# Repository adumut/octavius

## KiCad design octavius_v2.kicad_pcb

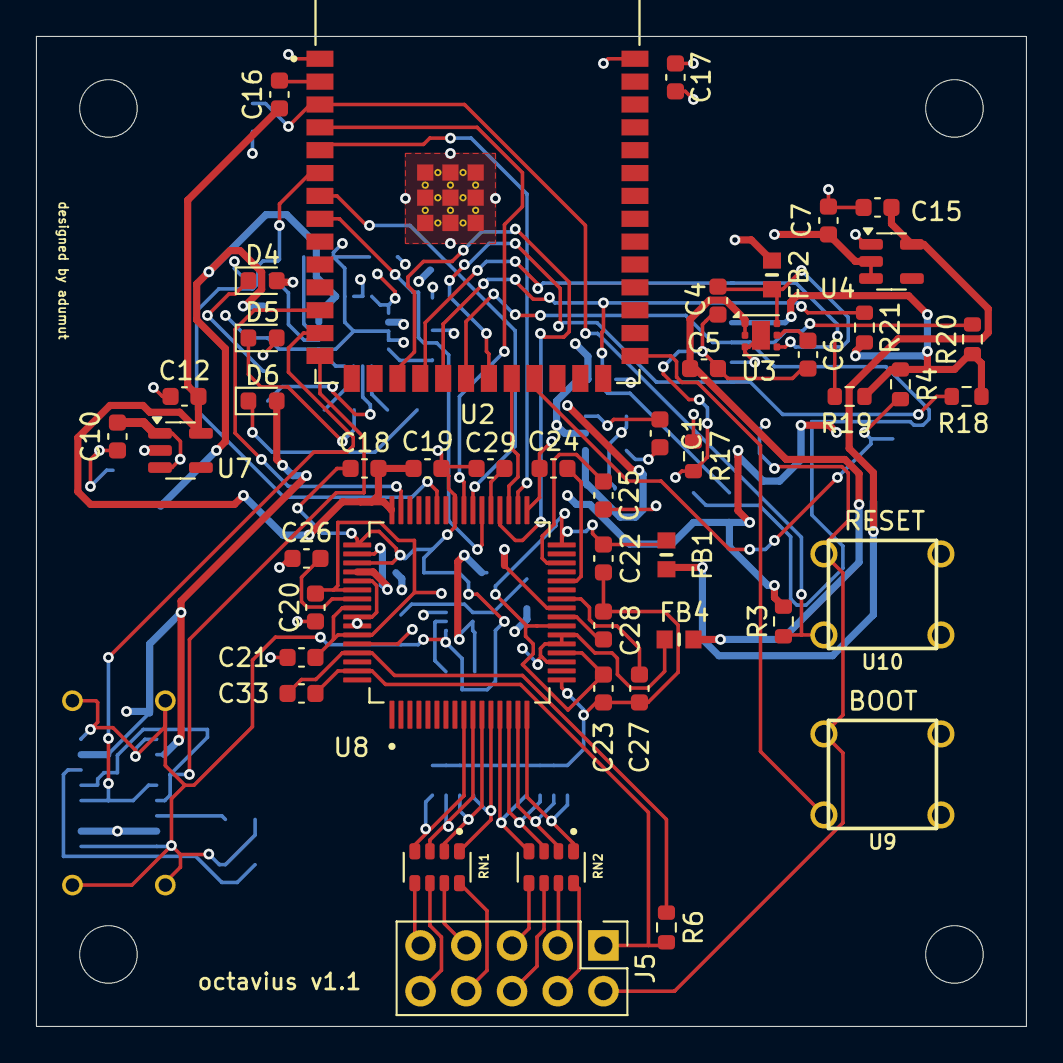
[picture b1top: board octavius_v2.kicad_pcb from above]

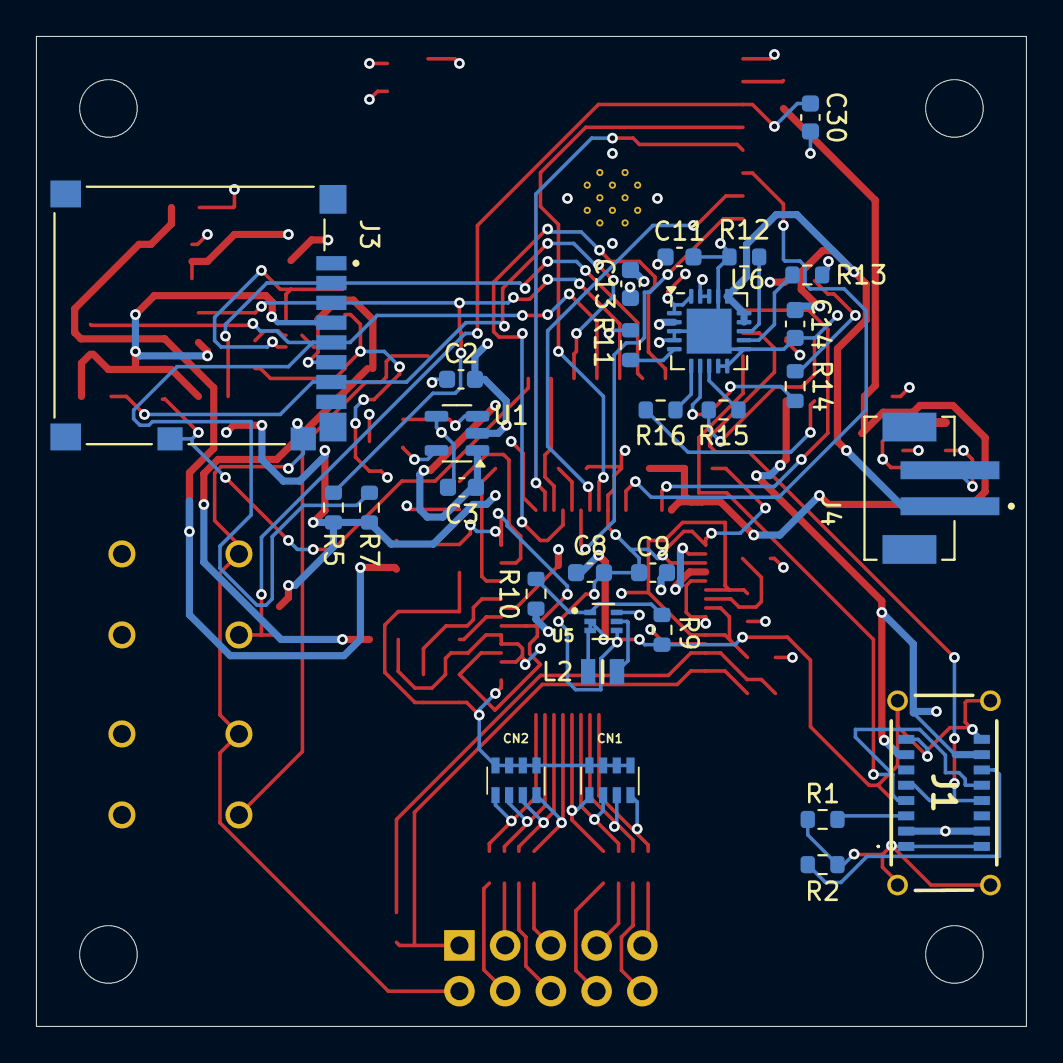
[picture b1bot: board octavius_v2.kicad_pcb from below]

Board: 4 copper layers, 55.0 x 55.0 mm, 76 parts (29 on the bottom side), 71 nets.

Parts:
C1, C2, C3, C6, C10, C12, C18, C21, C23, C25, C26, C27, C28, C30: 1uF; C_0603_1608Metric
C4, C5, C7, C15, C24: 2.2uF; C_0603_1608Metric
C8, C11, C16: 10uF; C_0603_1608Metric
C9: 22uF; C_0603_1608Metric
C13, C14: 4.7uF; C_0603_1608Metric
C17: 0.1uF; C_0603_1608Metric
C19, C20, C22: 100nF; C_0603_1608Metric
C29: 1nF; C_0603_1608Metric
C33: 1.5nF; C_0603_1608Metric
CN1, CN2: W3A45C103KAT2A (0.01uF); W3A45C103KAT2A
D4, D5, D6: LED; LED_0603_1608Metric
FB1, FB2, FB4: FerriteBead; BEADC1608X75N
J1: UJ20-C-V-SMT-TR-68; UJ20CVSMTTR68
J3: 5027740891; MOLEX_5027740891
J4: B2B-PH-SM4-TB; JST_B2B-PH-SM4-TB
J5: Conn_02x05_Odd_Even; PinHeader_2x05_P2.54mm_Vertical
L2: 2.2uH; DFE201210S1R0MP2
R1, R2: 5.1K; R_0603_1608Metric
R3, R4, R5, R7, R11, R18, R19, R20, R21: 10K; R_0603_1608Metric
R6: 1M; R_0603_1608Metric
R9: 100K; R_0603_1608Metric
R10: 732K; R_0603_1608Metric
R12, R13: 2K; R_0603_1608Metric
R14, R15, R16: 470; R_0603_1608Metric
R17: 0; R_0603_1608Metric
RN1, RN2: YC164-JR-072K2L (2.2K); YC164-JR-072K2L
U1: TPS60403DBV; SOT-23-5
U2: ESP32-S3-WROOM-1-N4R2
U3: ADP7118ACPZN; LFCSP-6-1EP_2x2mm_P0.65mm_EP1x1.6mm
U4: ADP7182AUJZ-2.5; TSOT-23-5
U5: TPS61023DRLT
U6: MCP73871; QFN-20-1EP_4x4mm_P0.5mm_EP2.5x2.5mm
U7: AP2112K-3.3; SOT-23-5
U8: ADS1299-4PAGR
U9, U10: JTP-1130

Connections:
1N: J5.3, RN2.7
1P: J5.4, RN2.8
2N: J5.5, RN2.5
2P: J5.6, RN2.6
3N: J5.7, RN1.7
3P: J5.8, RN1.8
4N: J5.9, RN1.5
4P: J5.10, RN1.6
-5V_RAW: C3.2, C7.2, U1.1 (OUT), U4.2 (VIN), U4.3 (EN)
/AFE/+2.5V_ANALOG: C5.1, FB4.2, U3.1 (VOUT), U3.2 (SENSE/ADJ)
/AFE/+3.3V: C12.2, C16.2, C18.2, C19.2, J3.4 (VDD), R3.2, R4.2, R5.1, R7.2, R18.2, R19.2, R20.1, R21.2, U7.5 (VOUT), U8.48 (DVDD), U8.50 (DVDD), U8.52 (CLKSEL)
/AFE/-2.5V_ANALOG: C15.2, FB1.1, U4.5 (VOUT), U8.25 (VREFN)
/AFE/AFE_CS: U2.7 (IO7), U8.39 (~CS)
/AFE/AFE_DRDY: U2.12 (IO8), U8.47 (~DRDY)
/AFE/AFE_MISO: U2.6 (IO6), U8.43 (DOUT)
/AFE/AFE_MOSI: U2.5 (IO5), U8.34 (DIN)
/AFE/AFE_RESET: U2.17 (IO9), U8.36 (~RESET)
/AFE/AFE_SCLK: U2.4 (IO4), U8.40 (SCLK)
/MCU_and_Connectors/USB_N: J1.A7 (DN1), J1.B7 (DN2), U2.13 (IO19)
/MCU_and_Connectors/USB_P: J1.A6 (DP1), J1.B6 (DP2), U2.14 (IO20)
/power_management/+5V_SYS: C2.2, C9.2, FB2.1, R10.2, U1.2 (IN), U5.6 (VOUT)
AGND: C4.2, C5.2, C6.2, C20.1, C21.2, C22.1, C23.2, C25.2, C26.1, C27.1, C28.1, CN1.5, CN1.6, CN1.7, CN1.8, CN2.5, CN2.6, CN2.7, CN2.8, R17.1, U8.17 (SRB1), U8.60 (BIASREF)
BIAS_OUT: C33.2, J5.1, R6.1, U8.63 (BIASOUT)
CHIP_PU: C30.1, R3.1, U2.3 (EN), U10.3
GND: C2.1, C3.1, C7.1, C8.1, C9.1, C10.2, C11.2, C12.1, C13.1, C14.2, C15.1, C17.1, C17.2, C18.1, C19.1, C24.2, C29.1, C30.2, J1.A1 (GND_1), J1.A12 (GND_2), J1.B1 (GND_3), J1.B12 (GND_4), J1.MH1, J1.MH2, J1.MH3, J1.MH4, J3.6 (VSS), J3.DN (DET_NAIL), J4.2, J5.2, R1.1, R2.2, R9.1, R11.2, R12.1, R13.1, R17.2, U1.4 (GND), U2.1 (GND), U2.40 (GND), U2.41_1 (GND), U2.41_2 (GND), U2.41_3 (GND), U2.41_4 (GND), U2.41_5 (GND), U2.41_6 (GND), U2.41_7 (GND), U2.41_8 (GND), U2.41_9 (GND), U2.41_10, U2.41_11, U2.41_12, U2.41_13, U2.41_14, U2.41_15, U2.41_16, U2.41_17, U2.41_18, U2.41_19, U2.41_20, U2.41_21, U3.3 (GND), U3.7 (GND), U4.1 (GND), U5.4 (GND), U6.3 (SEL), U6.4 (PROG2), U6.9 (~TE), U6.10 (V_{SS}), U6.11 (V_{SS}), U6.17 (CE), U6.21 (V_{SS}), U7.2 (GND), U8.33 (DGND), U8.41 (DAISY_IN), U8.49 (DGND), U8.51 (DGND), U9.1, U10.1
GPIO0: U2.27 (IO0), U9.3
IN1N_RAW: CN2.3, RN2.2, U8.15 (IN1N)
IN1P_RAW: CN2.4, RN2.1, U8.16 (IN1P)
IN2N_RAW: CN2.1, RN2.4, U8.13 (IN2N)
IN2P_RAW: CN2.2, RN2.3, U8.14 (IN2P)
IN3N_RAW: CN1.3, RN1.2, U8.11 (IN3N)
IN3P_RAW: CN1.4, RN1.1, U8.12 (IN3P)
IN4N_RAW: CN1.1, RN1.4, U8.9 (IN4N)
IN4P_RAW: CN1.2, RN1.3, U8.10 (IN4P)
unnamed: D4.1 (K), R14.2
unnamed: D5.1 (K), R15.2
unnamed: D6.1 (K), R16.2
unnamed: J1.A5 (CC1), R1.2
unnamed: J1.B5 (CC2), R2.1
unnamed: C1.1, U1.5 (C_{FLY+})
unnamed: C1.2, U1.3 (C_{FLY-})
unnamed: C16.1, U2.2 (3V3)
unnamed: C4.1, FB2.2, U3.4 (EN), U3.6 (VIN)
unnamed: C6.1, U3.5 (SS)
unnamed: R9.2, R10.1, U5.1 (FB)
unnamed: L2.2, U5.5 (SW)
unnamed: R12.2, U6.13 (PROG1)
unnamed: R13.2, U6.12 (PROG3)
unnamed: R15.1, U6.8 (STAT1/~LBO)
unnamed: R14.1, U6.7 (STAT2)
unnamed: R11.1, U6.5 (THERM)
unnamed: R16.1, U6.6 (~PG)
unnamed: C20.2, C21.1, FB4.1, U8.19 (AVDD@1), U8.21 (AVDD@1), U8.22 (AVDD@1), U8.54 (AVDD1), U8.56 (AVDD@1), U8.59 (AVDD@2)
unnamed: C22.2, C23.1, FB1.2, U8.20 (AVSS@1), U8.23 (AVSS@1), U8.32 (AVSS@1), U8.53 (AVSS1), U8.57 (AVSS@1), U8.58 (AVSS@2)
unnamed: C33.1, R6.2, U8.61 (BIASINV)
unnamed: C29.2, U8.37 (CLK)
unnamed: C24.1, U8.28 (VCAP1)
unnamed: C25.1, U8.30 (VCAP2)
unnamed: C26.2, U8.55 (VCAP3)
unnamed: C27.2, U8.26 (VCAP4)
unnamed: C28.2, U8.24 (VREFP)
PWDN: U2.22 (IO14), U8.35 (~PWDN)
SD_CS: J3.2 (CD/DAT3), R19.1, U2.18 (IO10)
SD_DETECT: J3.SN (SW_NAIL), R4.1, U2.23 (IO21)
SPI_MISO: J3.7 (DAT0), R18.1, U2.21 (IO13)
SPI_MOSI: J3.3 (CMD), R7.1, R21.1, U2.19 (IO11)
SPI_SCLK: J3.5 (CLK), R5.2, R20.2, U2.20 (IO12)
START: U2.8 (IO15), U8.38 (START)
SYS_LOAD: C8.2, C10.1, C13.2, L2.1, U5.2 (EN), U5.3 (VIN), U6.1 (OUT), U6.20 (OUT), U7.1 (VIN), U7.3 (EN)
VBAT: C14.1, J4.1, U6.14 (V_{BAT}), U6.15 (V_{BAT}), U6.16 (V_{BAT_SENSE})
VBUS: C11.1, D4.2 (A), D5.2 (A), D6.2 (A), J1.A4 (VBUS_1), J1.A9 (VBUS_2), J1.B4 (VBUS_3), J1.B9 (VBUS_4), U6.2 (VPCC), U6.18 (IN), U6.19 (IN)

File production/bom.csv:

Designator,Footprint,Quantity,Value,LCSC Part #
ANT1,ANTC3216X140N,1,2450AT18B0100001E,
"C1, C10, C12, C18, C2, C21, C23, C25, C26, C27, C28, C3, C6",0603,13,1uF,
"C11, C8",0603,2,10uF,
"C13, C14",0603,2,4.7uF,
"C15, C24, C4, C5, C7",0603,5,2.2uF,
"C16, C17, C19, C20, C22",0603,5,100nF,
C29,0603,1,1nF,
C30,0402,1,1pF,
C31,0402,1,2.2pF,
C32,0402,1,100pF,
C33,0603,1,1.5nF,
C9,0603,1,22uF,
"CN1, CN2",W3A45C103KAT2A,2,W3A45C103KAT2A (0.01uF),
"D4, D5, D6",0603,3,LED,
"FB1, FB2, FB4, FB5",BEADC1608X75N,4,FerriteBead,
J1,UJ20CVSMTTR68,1,UJ20-C-V-SMT-TR-68,
J2,GTFH08131YHR,1,GTFH08131YHR,
J3,512810898,1,51281-0898,
J4,JST_B2B-PH-SM4-TB,1,B2B-PH-SM4-TB,
J5,PinHeader_2x05_P1.00mm_Horizontal,1,Conn_02x05_Odd_Even,
L1,DFE201210S1R0MP2,1,3.9nH,
L2,DFE201210S1R0MP2,1,2.2uH,
Q1,SOT-23,1,2N7002,
"R1, R11, R2, R7",0603,4,10K,
R10,0603,1,910K,
"R12, R13",0603,2,2K,
"R14, R15, R16",0603,3,470,
"R3, R4",0603,2,5.1K,
R5,0603,1,1K,
R6,0603,1,1M,
R9,0603,1,100K,
"RN1, RN2",ACASA1001S2001P100,2,ACASA1001S2001P100 (1K),
U1,SOT-23-5,1,TPS60403DBV,
"U10, U9",JTP-1130,2,JTP-1130,
U2,QFN-56-1EP_7x7mm_P0.4mm_EP4x4mm,1,ESP32-S3,
U3,LFCSP-6-1EP_2x2mm_P0.65mm_EP1x1.6mm,1,ADP7118ACPZN,
U4,TSOT-23-5,1,ADP7182AUJZ-2.5,
U5,TPS61023DRLT,1,TPS61023DRLT,
U6,QFN-20-1EP_4x4mm_P0.5mm_EP2.5x2.5mm,1,MCP73871,
U7,SOT-23-5,1,AP2112K-3.3,
U8,ADS1299-4PAGR,1,ADS1299-4PAGR,
